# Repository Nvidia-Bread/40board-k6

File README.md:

# 40board-k6
A 40% low profile keyboard with a knob (made in kicad 6)

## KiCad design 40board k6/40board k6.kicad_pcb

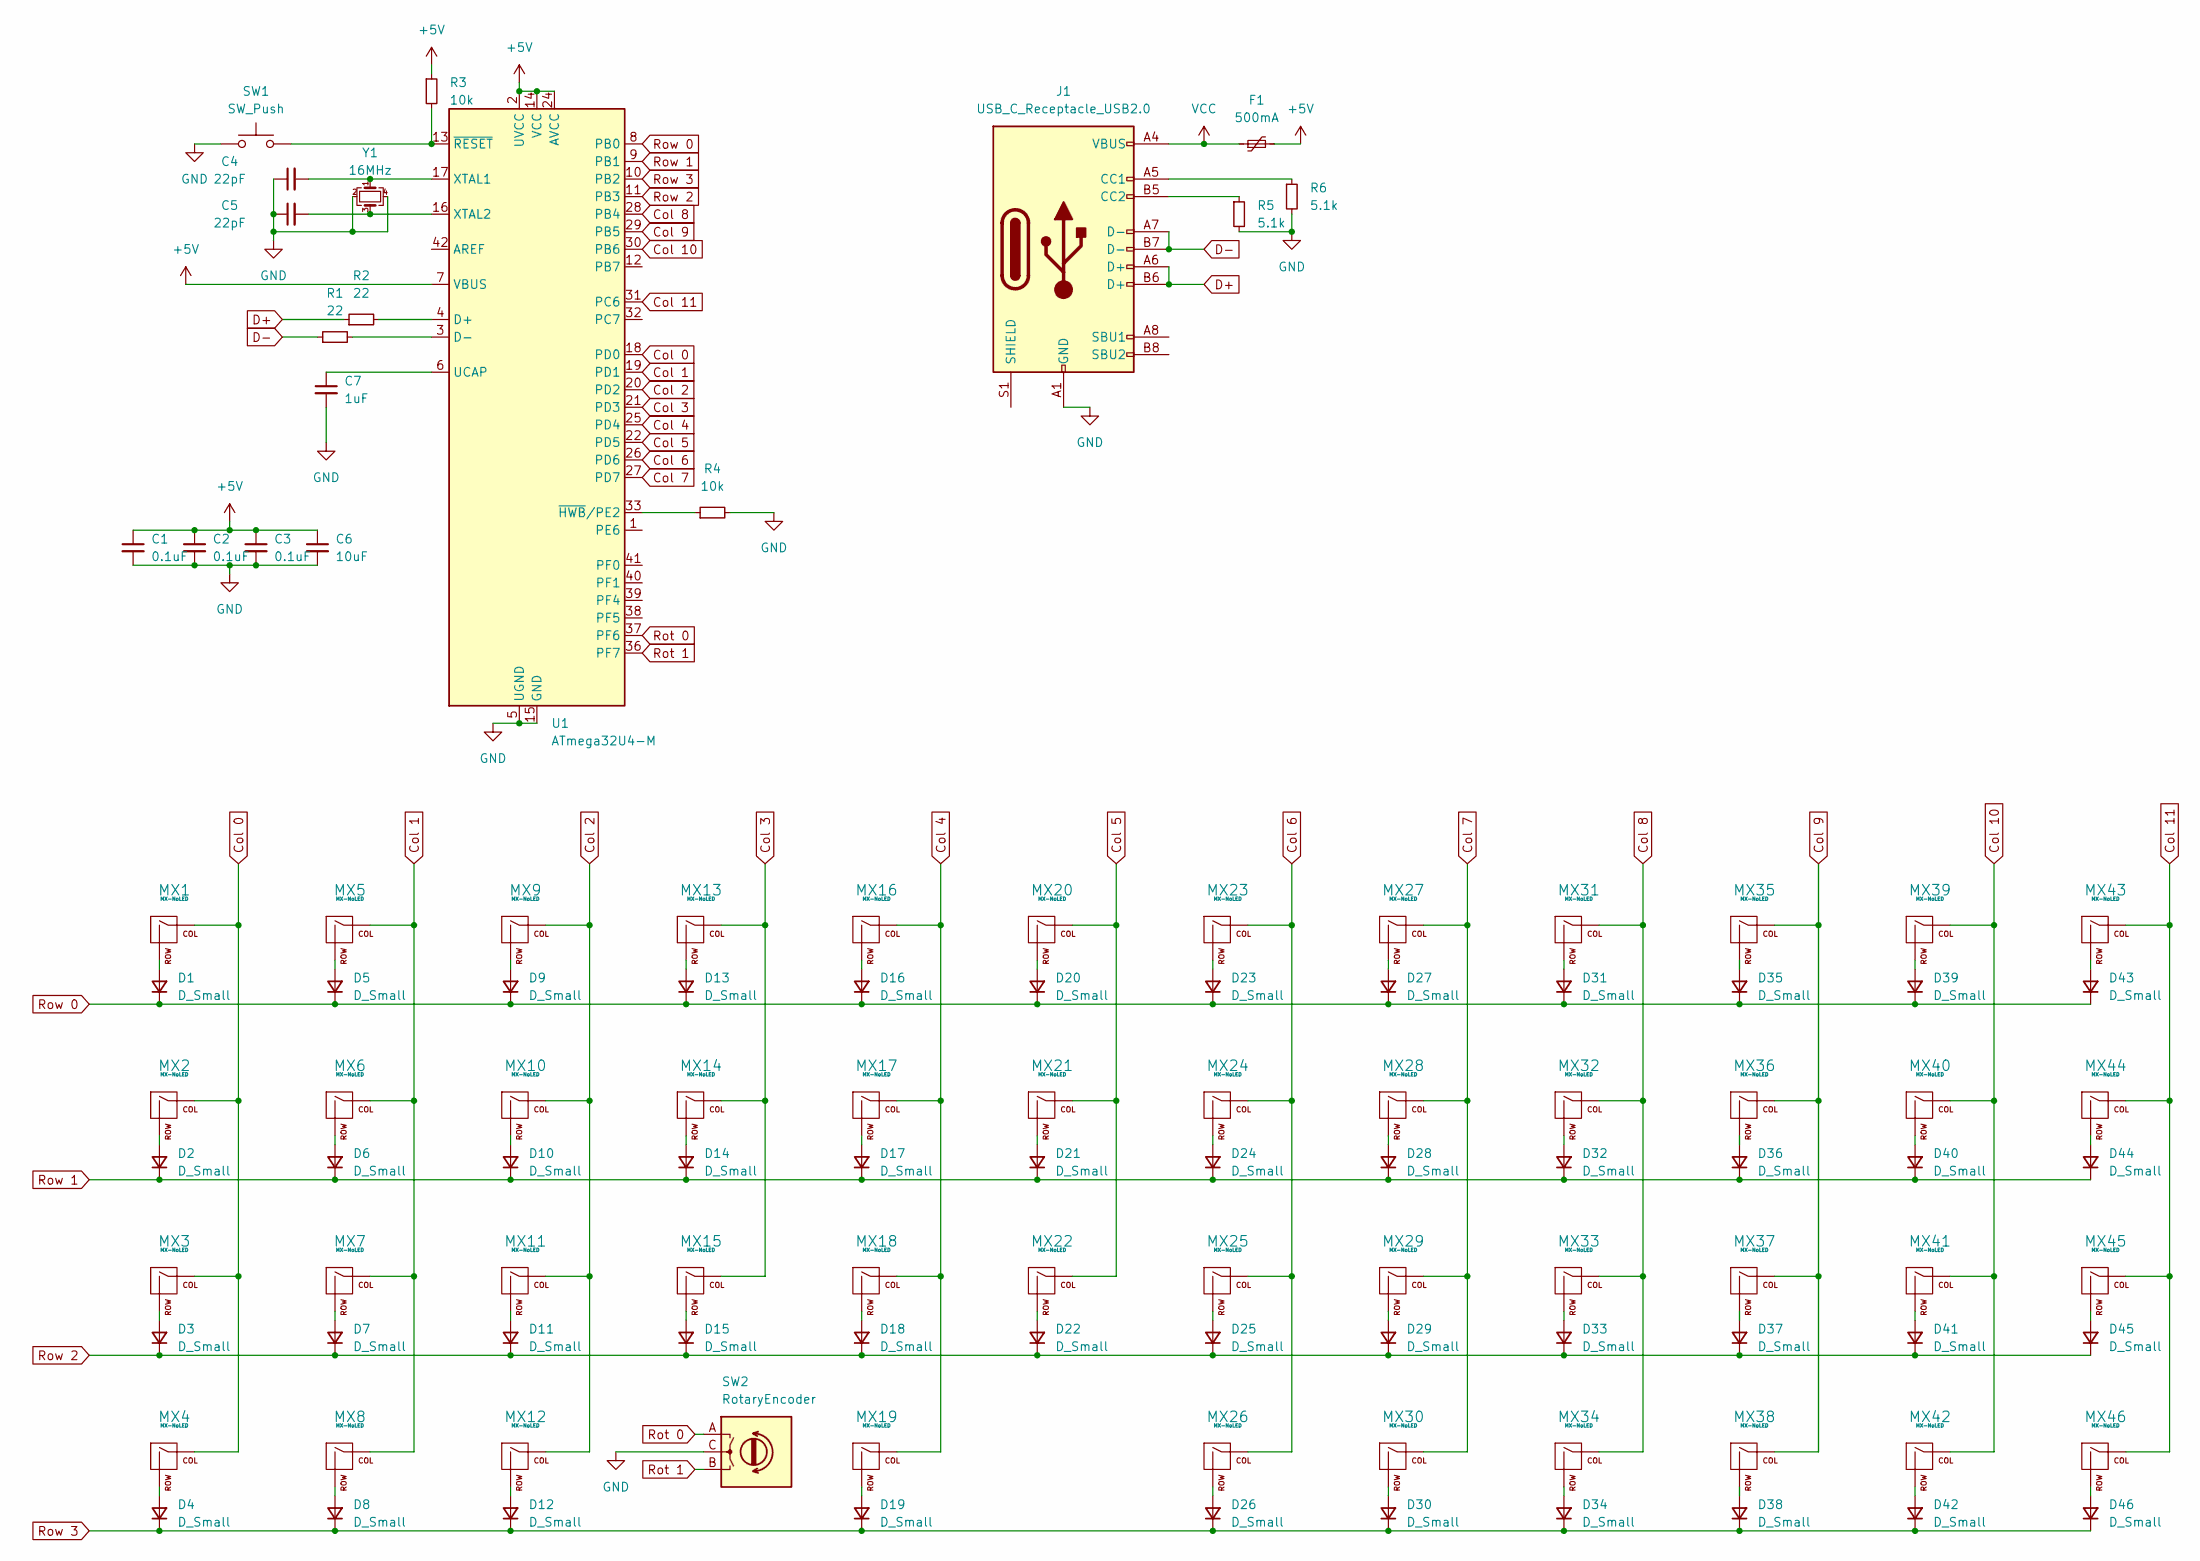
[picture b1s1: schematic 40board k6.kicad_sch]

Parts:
C1, C2, C3: 0.1uF; C_0805_2012Metric
C4, C5: 22pF; C_0805_2012Metric
C6: 10uF; C_0805_2012Metric
C7: 1uF; D_0805_2012Metric
D1, D2, D3, D4, D5, D6, D7, D8, D9, D10, D11, D12, D13, D14, D15, D16, D17, D18, D19, D20, D21, D22, D23, D24, D25, D26, D27, D28, D29, D30, D31, D32, D33, D34, D35, D36, D37, D38, D39, D40, D41, D42, D43, D44, D45, D46: D_Small; D_SOD-123
F1: 500mA; Fuse_1206_3216Metric
J1: USB_C_Receptacle_USB2.0; USB_C_Receptacle_HRO_TYPE-C-31-M-14
MX1, MX2, MX3, MX4, MX5, MX6, MX7, MX8, MX9, MX10, MX11, MX12, MX13, MX14, MX15, MX16, MX17, MX18, MX19, MX20, MX21, MX22, MX23, MX24, MX25, MX26, MX27, MX28, MX29, MX30, MX31, MX32, MX33, MX34, MX35, MX36, MX37, MX38, MX39, MX40, MX41, MX42, MX43, MX44, MX45, MX46: MX-NoLED; KailhChoc-1U
R1, R2: 22; R_0805_2012Metric
R3, R4: 10k; R_0805_2012Metric
R5, R6: 5.1k; R_0805_2012Metric
SW1: SW_Push; SKQG-1155865
SW2: RotaryEncoder; RotaryEncoder_Alps_EC12E_Vertical_H20mm
U1: ATmega32U4-M; QFN-44-1EP_7x7mm_P0.5mm_EP5.2x5.2mm
Y1: 16MHz; Crystal_SMD_3225-4Pin_3.2x2.5mm

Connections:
+5V: C1.1, C2.1, C3.1, C6.1, F1.2, R3.1, U1.2 (UVCC), U1.7 (VBUS), U1.14 (VCC), U1.24 (AVCC), U1.34 (VCC), U1.44 (AVCC)
Col 0: MX1.1 (COL), MX2.1 (COL), MX3.1 (COL), MX4.1 (COL), U1.18 (PD0)
Col 1: MX5.1 (COL), MX6.1 (COL), MX7.1 (COL), MX8.1 (COL), U1.19 (PD1)
Col 2: MX9.1 (COL), MX10.1 (COL), MX11.1 (COL), MX12.1 (COL), U1.20 (PD2)
Col 3: MX13.1 (COL), MX14.1 (COL), MX15.1 (COL), U1.21 (PD3)
Col 4: MX16.1 (COL), MX17.1 (COL), MX18.1 (COL), MX19.1 (COL), U1.25 (PD4)
Col 5: MX20.1 (COL), MX21.1 (COL), MX22.1 (COL), U1.22 (PD5)
Col 6: MX23.1 (COL), MX24.1 (COL), MX25.1 (COL), MX26.1 (COL), U1.26 (PD6)
Col 7: MX27.1 (COL), MX28.1 (COL), MX29.1 (COL), MX30.1 (COL), U1.27 (PD7)
Col 8: MX31.1 (COL), MX32.1 (COL), MX33.1 (COL), MX34.1 (COL), U1.28 (PB4)
Col 9: MX35.1 (COL), MX36.1 (COL), MX37.1 (COL), MX38.1 (COL), U1.29 (PB5)
Col 10: MX39.1 (COL), MX40.1 (COL), MX41.1 (COL), MX42.1 (COL), U1.30 (PB6)
Col 11: MX43.1 (COL), MX44.1 (COL), MX45.1 (COL), MX46.1 (COL), U1.31 (PC6)
D+: J1.A6 (D+), J1.B6 (D+), R2.1
D-: J1.A7 (D-), J1.B7 (D-), R1.1
GND: C1.2, C2.2, C3.2, C4.1, C5.1, C6.2, C7.2, J1.A1 (GND), J1.A12 (GND), J1.B1 (GND), J1.B12 (GND), R4.2, R5.2, R6.2, SW1.1, SW2.C, U1.5 (UGND), U1.15 (GND), U1.23 (GND), U1.35 (GND), U1.43 (GND), U1.45 (GND), Y1.2, Y1.4
unnamed: C4.2, U1.17 (XTAL1), Y1.1
unnamed: C5.2, U1.16 (XTAL2), Y1.3
unnamed: C7.1, U1.6 (UCAP)
unnamed: D1.2 (A), MX1.2 (ROW)
unnamed: D2.2 (A), MX2.2 (ROW)
unnamed: D3.2 (A), MX3.2 (ROW)
unnamed: D4.2 (A), MX4.2 (ROW)
unnamed: D5.2 (A), MX5.2 (ROW)
unnamed: D6.2 (A), MX6.2 (ROW)
unnamed: D7.2 (A), MX7.2 (ROW)
unnamed: D8.2 (A), MX8.2 (ROW)
unnamed: D9.2 (A), MX9.2 (ROW)
unnamed: D10.2 (A), MX10.2 (ROW)
unnamed: D11.2 (A), MX11.2 (ROW)
unnamed: D12.2 (A), MX12.2 (ROW)
unnamed: D13.2 (A), MX13.2 (ROW)
unnamed: D14.2 (A), MX14.2 (ROW)
unnamed: D15.2 (A), MX15.2 (ROW)
unnamed: D16.2 (A), MX16.2 (ROW)
unnamed: D17.2 (A), MX17.2 (ROW)
unnamed: D18.2 (A), MX18.2 (ROW)
unnamed: D19.2 (A), MX19.2 (ROW)
unnamed: D20.2 (A), MX20.2 (ROW)
unnamed: D21.2 (A), MX21.2 (ROW)
unnamed: D22.2 (A), MX22.2 (ROW)
unnamed: D23.2 (A), MX23.2 (ROW)
unnamed: D24.2 (A), MX24.2 (ROW)
unnamed: D25.2 (A), MX25.2 (ROW)
unnamed: D26.2 (A), MX26.2 (ROW)
unnamed: D27.2 (A), MX27.2 (ROW)
unnamed: D28.2 (A), MX28.2 (ROW)
unnamed: D29.2 (A), MX29.2 (ROW)
unnamed: D30.2 (A), MX30.2 (ROW)
unnamed: D31.2 (A), MX31.2 (ROW)
unnamed: D32.2 (A), MX32.2 (ROW)
unnamed: D33.2 (A), MX33.2 (ROW)
unnamed: D34.2 (A), MX34.2 (ROW)
unnamed: D35.2 (A), MX35.2 (ROW)
unnamed: D36.2 (A), MX36.2 (ROW)
unnamed: D37.2 (A), MX37.2 (ROW)
unnamed: D38.2 (A), MX38.2 (ROW)
unnamed: D39.2 (A), MX39.2 (ROW)
unnamed: D40.2 (A), MX40.2 (ROW)
unnamed: D41.2 (A), MX41.2 (ROW)
unnamed: D42.2 (A), MX42.2 (ROW)
unnamed: D43.2 (A), MX43.2 (ROW)
unnamed: D44.2 (A), MX44.2 (ROW)
unnamed: D45.2 (A), MX45.2 (ROW)
unnamed: D46.2 (A), MX46.2 (ROW)
unnamed: J1.A5 (CC1), R6.1
unnamed: J1.B5 (CC2), R5.1
unnamed: R1.2, U1.3 (D-)
unnamed: R2.2, U1.4 (D+)
unnamed: R3.2, SW1.2, U1.13 (~RESET)
unnamed: R4.1, U1.33 (~HWB/PE2)
Rot 0: SW2.A, U1.37 (PF6)
Rot 1: SW2.B, U1.36 (PF7)
Row 0: D1.1 (K), D5.1 (K), D9.1 (K), D13.1 (K), D16.1 (K), D20.1 (K), D23.1 (K), D27.1 (K), D31.1 (K), D35.1 (K), D39.1 (K), D43.1 (K), U1.8 (PB0)
Row 1: D2.1 (K), D6.1 (K), D10.1 (K), D14.1 (K), D17.1 (K), D21.1 (K), D24.1 (K), D28.1 (K), D32.1 (K), D36.1 (K), D40.1 (K), D44.1 (K), U1.9 (PB1)
Row 2: D3.1 (K), D7.1 (K), D11.1 (K), D15.1 (K), D18.1 (K), D22.1 (K), D25.1 (K), D29.1 (K), D33.1 (K), D37.1 (K), D41.1 (K), D45.1 (K), U1.11 (PB3)
Row 3: D4.1 (K), D8.1 (K), D12.1 (K), D19.1 (K), D26.1 (K), D30.1 (K), D34.1 (K), D38.1 (K), D42.1 (K), D46.1 (K), U1.10 (PB2)
VCC: F1.1, J1.A4 (VBUS), J1.A9 (VBUS), J1.B4 (VBUS), J1.B9 (VBUS)

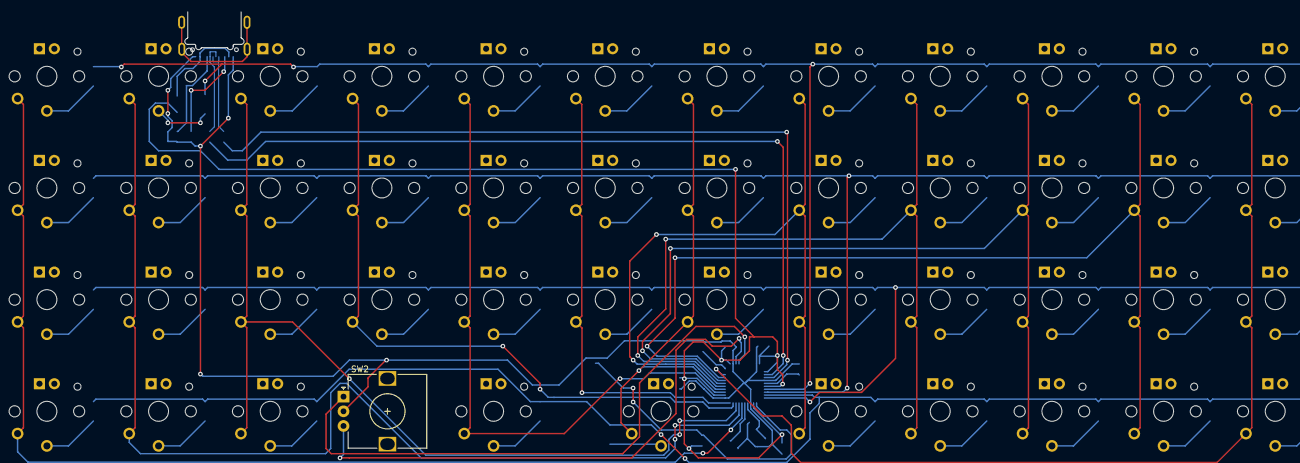
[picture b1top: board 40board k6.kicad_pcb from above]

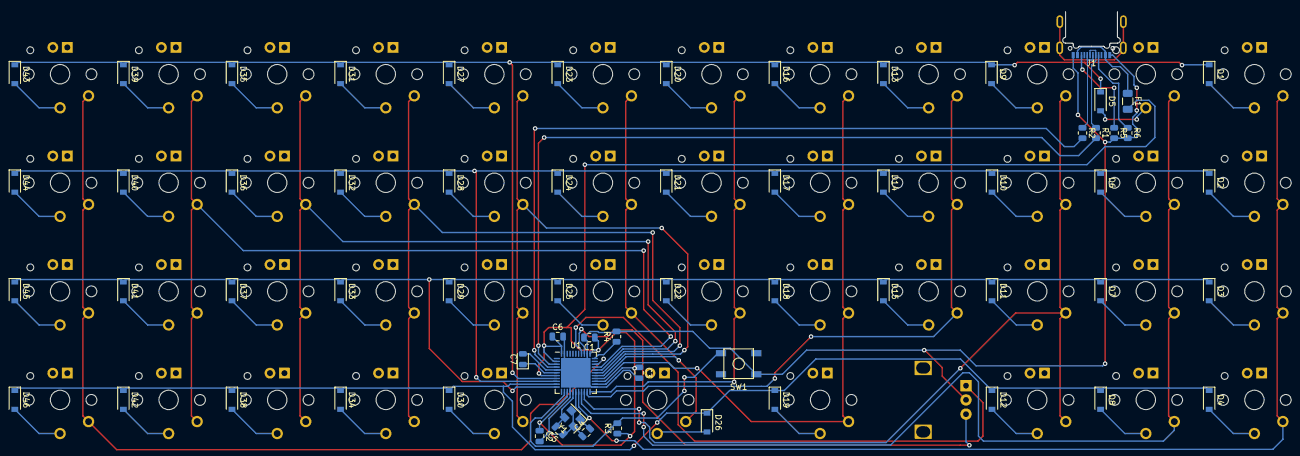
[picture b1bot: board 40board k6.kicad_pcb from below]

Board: 2 copper layers, 111 parts (64 on the bottom side), 78 nets.

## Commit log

2023-10-09 Initialize project
2023-10-09 Added footprint/symbol libs
2023-10-10 Finished MCU
2023-10-11 Finished Schematic
2023-10-11 Added Marbastlib and annotations
2023-10-12 Finished placing footprints
2023-10-12 Finished routing PCB
2023-10-16 Added edge cuts + ground fills
